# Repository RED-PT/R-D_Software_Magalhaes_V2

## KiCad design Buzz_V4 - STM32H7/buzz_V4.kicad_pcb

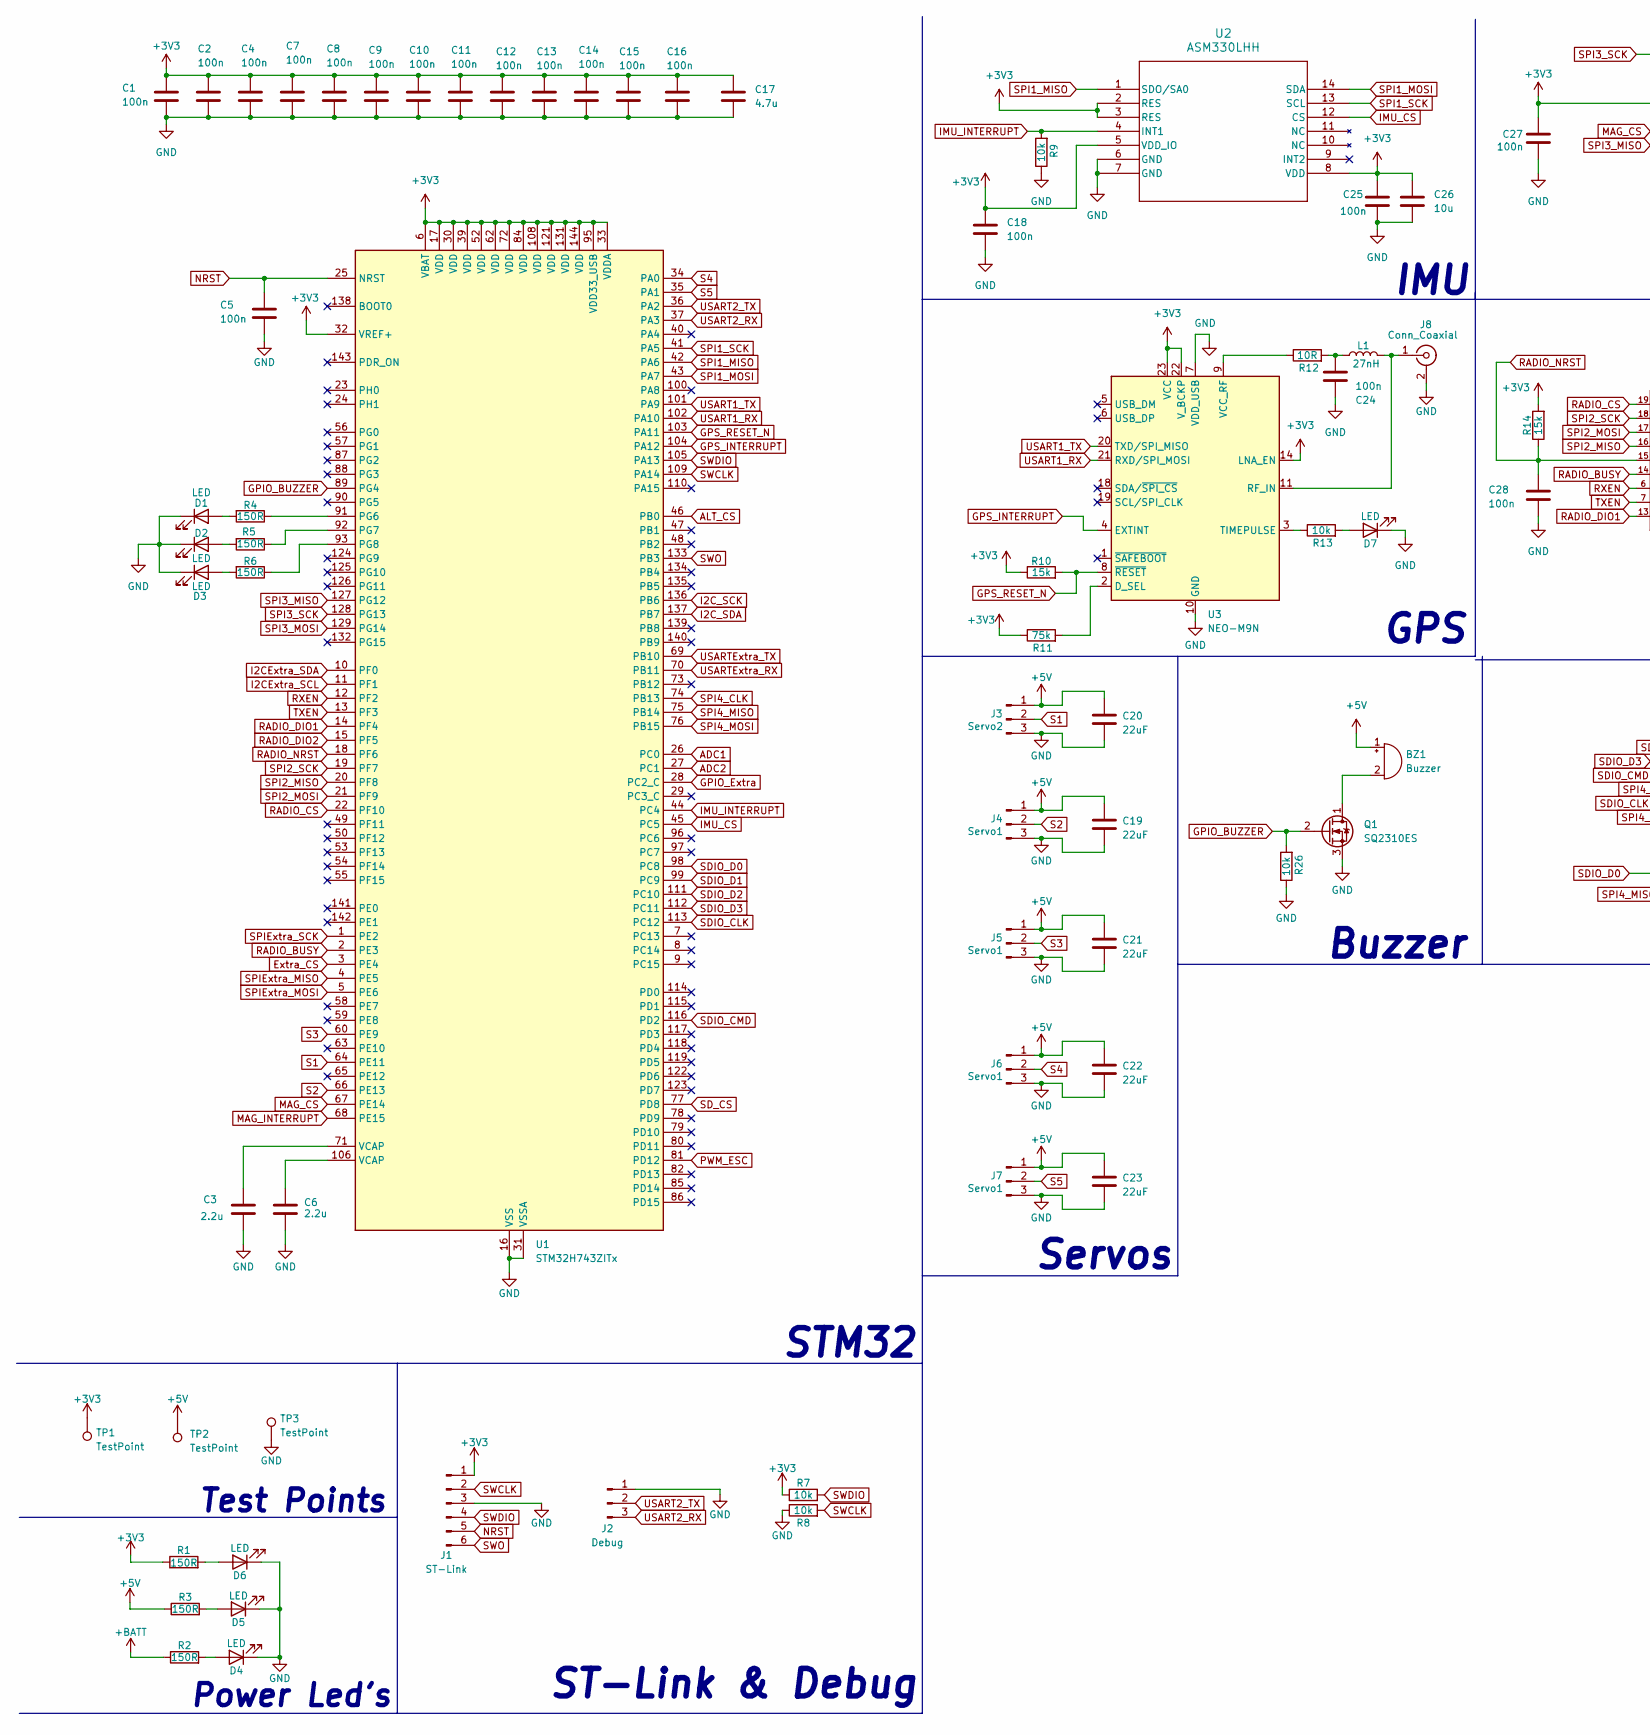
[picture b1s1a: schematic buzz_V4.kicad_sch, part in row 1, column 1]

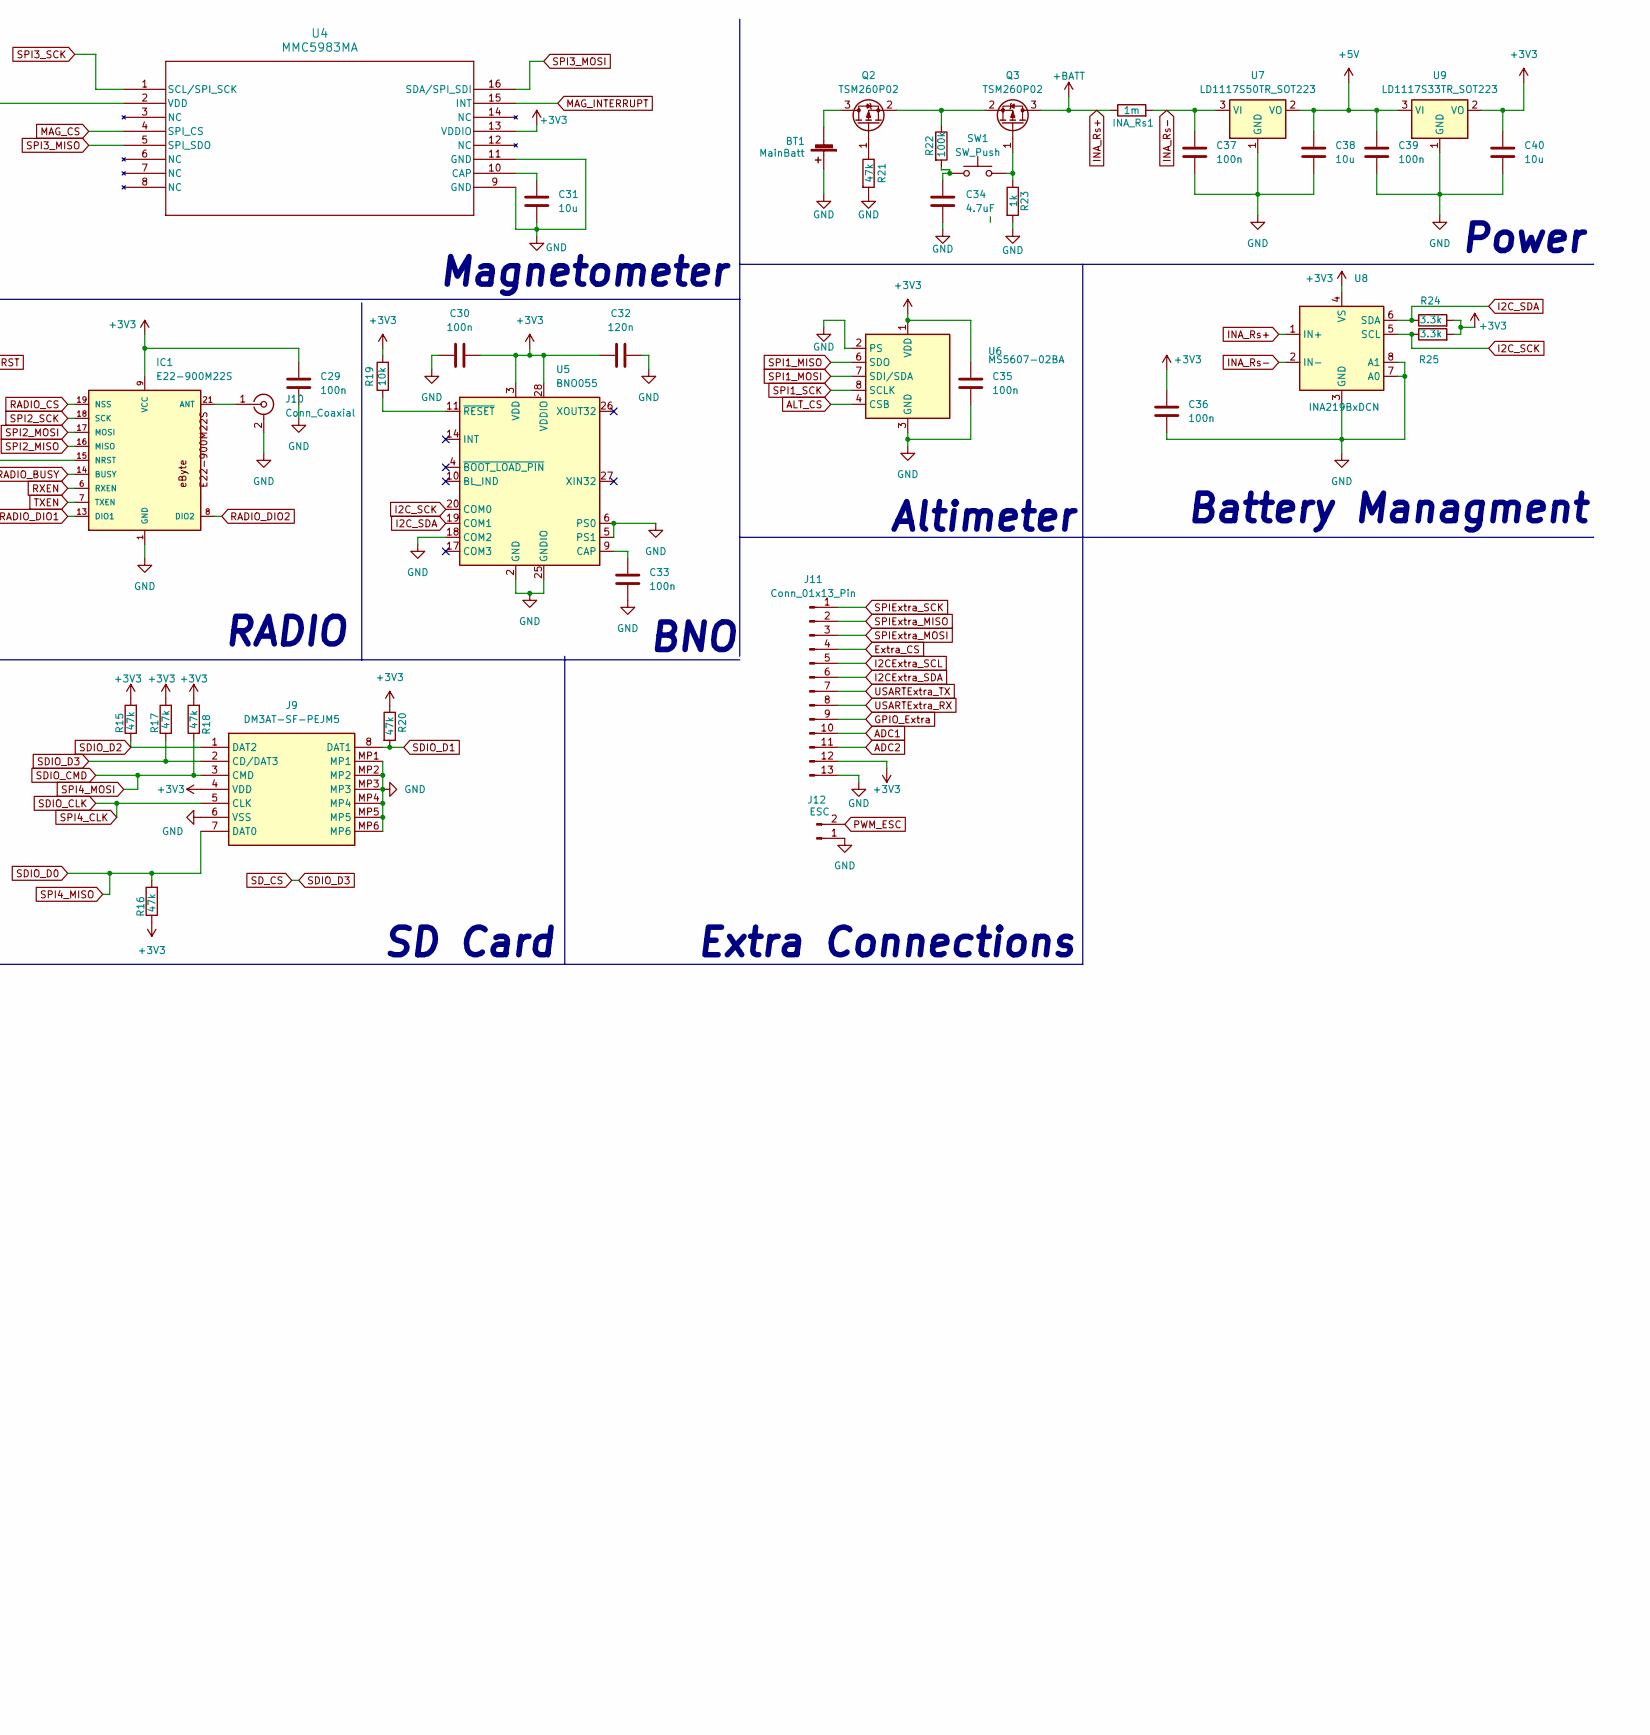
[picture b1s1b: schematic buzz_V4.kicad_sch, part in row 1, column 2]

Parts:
BT1: MainBatt; AMASS_XT30U-M_1x02_P5.0mm_Vertical
BZ1: Buzzer; Buzzer_12x9.5RM7.6
C1, C2, C4, C5, C7, C8, C9, C10, C11, C12, C13, C14, C15, C16, C18, C24, C25, C27, C28, C29, C30, C33, C35, C36, C37, C39: 100n; C_1206_3216Metric_Pad1.33x1.80mm_HandSolder
C3, C6: 2.2u; C_1206_3216Metric_Pad1.33x1.80mm_HandSolder
C17: 4.7u; C_1206_3216Metric_Pad1.33x1.80mm_HandSolder
C19, C20, C21, C22, C23: 22uF; C_1206_3216Metric_Pad1.33x1.80mm_HandSolder
C26, C31, C38, C40: 10u; C_1206_3216Metric_Pad1.33x1.80mm_HandSolder
C32: 120n; C_1206_3216Metric_Pad1.33x1.80mm_HandSolder
C34: 4.7uF; C_1206_3216Metric_Pad1.33x1.80mm_HandSolder
D1, D2, D3, D4, D5, D6, D7: LED; LED_0805_2012Metric_Pad1.15x1.40mm_HandSolder
IC1: E22-900M22S
INA_Rs1: 1m; R_2512_6332Metric_Pad1.40x3.35mm_HandSolder
J1: ST-Link; PinHeader_1x06_P2.54mm_Vertical
J2: Debug; PinHeader_1x03_P2.54mm_Vertical
J3: Servo2; PinHeader_1x03_P2.54mm_Vertical
J4, J5, J6, J7: Servo1; PinHeader_1x03_P2.54mm_Vertical
J8: Conn_Coaxial; U.FL_Molex_MCRF_73412-0110_Vertical
J9: DM3AT-SF-PEJM5; DM3ATSFPEJM5; Mouser Part Number 798-DM3AT-SF-PEJM5
J10: Conn_Coaxial; SMA_Amphenol_132134-10_Vertical
J11: Conn_01x13_Pin; PinHeader_1x13_P2.54mm_Vertical
J12: ESC; PinHeader_1x02_P2.54mm_Vertical
L1: 27nH; L_0603_1608Metric_Pad1.05x0.95mm_HandSolder
Q1: SQ2310ES; SOT-23
Q2, Q3: TSM260P02; SOT-23
R1, R2, R3, R4, R5, R6: 150R; R_0805_2012Metric_Pad1.20x1.40mm_HandSolder
R7, R8, R9, R13, R19, R26: 10k; R_0805_2012Metric_Pad1.20x1.40mm_HandSolder
R10, R14: 15k; R_0805_2012Metric_Pad1.20x1.40mm_HandSolder
R11: 75k; R_0805_2012Metric_Pad1.20x1.40mm_HandSolder
R12: 10R; R_0805_2012Metric_Pad1.20x1.40mm_HandSolder
R15, R16, R17, R18, R20, R21: 47k; R_0805_2012Metric_Pad1.20x1.40mm_HandSolder
R22: 100k; R_0805_2012Metric_Pad1.20x1.40mm_HandSolder
R23: 1k; R_0805_2012Metric_Pad1.20x1.40mm_HandSolder
R24, R25: 3.3k; R_0805_2012Metric_Pad1.20x1.40mm_HandSolder
SW1: SW_Push; SW_PUSH_6mm
TP1, TP2, TP3: TestPoint; TestPoint_Plated_Hole_D2.0mm
U1: STM32H743ZITx; LQFP-144_20x20mm_P0.5mm
U2: ASM330LHH; LGA-14L_2P5X3X0P83_STM
U3: NEO-M9N; ublox_NEO
U4: MMC5983MA; MMC5983MA_MEM
U5: BNO055; LGA-28_5.2x3.8mm_P0.5mm
U6: MS5607-02BA; LGA-8_3x5mm_P1.25mm
U7: LD1117S50TR_SOT223; SOT-223-3_TabPin2
U8: INA219BxDCN; SOT-23-8
U9: LD1117S33TR_SOT223; SOT-223-3_TabPin2

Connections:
+3V3: C1.1, C2.1, C4.1, C7.1, C8.1, C9.1, C10.1, C11.1, C12.1, C13.1, C14.1, C15.1, C16.1, C17.1, C18.1, C25.1, C26.1, C27.1, C29.1, C30.2, C32.1, C35.1, C36.1, C40.1, IC1.9 (VCC), J1.1, J9.4 (VDD), J11.12, R1.1, R7.1, R10.1, R11.1, R14.2, R15.2, R16.1, R17.2, R18.2, R19.2, R20.1, R24.2, R25.2, TP1.1, U1.6 (VBAT), U1.17 (VDD), U1.30 (VDD), U1.32 (VREF+), U1.33 (VDDA), U1.39 (VDD), U1.52 (VDD), U1.62 (VDD), U1.72 (VDD), U1.84 (VDD), U1.95 (VDD33_USB), U1.108 (VDD), U1.121 (VDD), U1.131 (VDD), U1.144 (VDD), U2.2 (RES), U2.3 (RES), U2.5 (VDD_IO), U2.8 (VDD), U3.14 (LNA_EN), U3.22 (V_BCKP), U3.23 (VCC), U4.2 (VDD), U4.13 (VDDIO), U5.3 (VDD), U5.28 (VDDIO), U6.1 (VDD), U8.4 (VS), U9.2 (VO)
+5V: BZ1.1 (+), C19.1, C20.1, C21.1, C22.1, C23.1, C38.1, C39.1, J3.1, J4.1, J5.1, J6.1, J7.1, R3.1, TP2.1, U7.2 (VO), U9.3 (VI)
ADC1: J11.10, U1.26 (PC0)
ADC2: J11.11, U1.27 (PC1)
ALT_CS: U1.46 (PB0), U6.4 (CSB), U6.5 (CSB)
Extra_CS: J11.4, U1.3 (PE4)
GND: BT1.1 (+), C1.2, C2.2, C3.2, C4.2, C5.2, C6.2, C7.2, C8.2, C9.2, C10.2, C11.2, C12.2, C13.2, C14.2, C15.2, C16.2, C17.2, C18.2, C19.2, C20.2, C21.2, C22.2, C23.2, C24.2, C25.2, C26.2, C27.2, C28.2, C29.2, C30.1, C31.2, C32.2, C33.2, C34.2, C35.2, C36.2, C37.2, C38.2, C39.2, C40.2, D1.1 (K), D2.1 (K), D3.1 (K), D4.1 (K), D5.1 (K), D6.1 (K), D7.1 (K), IC1.1 (GND), IC1.2 (GND), IC1.3 (GND), IC1.4 (GND), IC1.5 (GND), IC1.10 (GND), IC1.11 (GND), IC1.12 (GND), IC1.20 (GND), IC1.22 (GND), J1.3, J2.1, J3.3, J4.3, J5.3, J6.3, J7.3, J8.2 (Ext), J9.6 (VSS), J9.MP1, J9.MP2, J9.MP3, J9.MP4, J9.MP5, J9.MP6, J10.2 (Ext), J11.13, J12.1, Q1.3 (S), R8.1, R9.1, R21.2, R23.2, R26.1, TP3.1, U1.16 (VSS), U1.31 (VSSA), U1.38 (VSS), U1.51 (VSS), U1.61 (VSS), U1.83 (VSS), U1.94 (VSS), U1.107 (VSS), U1.120 (VSS), U1.130 (VSS), U2.6 (GND), U2.7 (GND), U3.7 (VDD_USB), U3.10 (GND), U3.12 (GND), U3.13 (GND), U3.24 (GND), U4.9 (GND), U4.11 (GND), U5.2 (GND), U5.5 (PS1), U5.6 (PS0), U5.18 (COM2), U5.25 (GNDIO), U6.2 (PS), U6.3 (GND), U7.1 (GND), U8.3 (GND), U8.7 (A0), U8.8 (A1), U9.1 (GND)
GPIO_BUZZER: Q1.2 (G), R26.2, U1.89 (PG4)
GPIO_Extra: J11.9, U1.28 (PC2_C)
GPS_INTERRUPT: U1.104 (PA12), U3.4 (EXTINT)
GPS_RESET_N: R10.2, U1.103 (PA11), U3.8 (~RESET)
I2CExtra_SCL: J11.5, U1.11 (PF1)
I2CExtra_SDA: J11.6, U1.10 (PF0)
I2C_SCK: R25.1, U1.136 (PB6), U5.20 (COM0), U8.5 (SCL)
I2C_SDA: R24.1, U1.137 (PB7), U5.19 (COM1), U8.6 (SDA)
IMU_CS: U1.45 (PC5), U2.12 (CS)
IMU_INTERRUPT: R9.2, U1.44 (PC4), U2.4 (INT1)
INA_Rs+: INA_Rs1.1, Q3.3 (D), R2.1, U8.1 (IN+)
INA_Rs-: C37.1, INA_Rs1.2, U7.3 (VI), U8.2 (IN-)
MAG_CS: U1.67 (PE14), U4.4 (SPI_CS)
MAG_INTERRUPT: U1.68 (PE15), U4.15 (INT)
NRST: C5.1, J1.5, U1.25 (NRST)
unnamed: BT1.2 (-), Q2.3 (D)
unnamed: BZ1.2 (-), Q1.1 (D)
unnamed: C3.1, U1.71 (VCAP)
unnamed: C6.1, U1.106 (VCAP)
unnamed: C24.1, L1.1, R12.2
unnamed: C34.1, R22.2, SW1.1
unnamed: D1.2 (A), R4.2
unnamed: D2.2 (A), R5.2
unnamed: D3.2 (A), R6.2
unnamed: D4.2 (A), R2.2
unnamed: D5.2 (A), R3.2
unnamed: D6.2 (A), R1.2
unnamed: D7.2 (A), R13.2
unnamed: IC1.21 (ANT), J10.1 (In)
unnamed: J8.1 (In), L1.2, U3.11 (RF_IN)
unnamed: Q2.1 (G), R21.1
unnamed: Q2.2 (S), Q3.2 (S), R22.1
unnamed: Q3.1 (G), R23.1, SW1.2
unnamed: R4.1, U1.91 (PG6)
unnamed: R5.1, U1.92 (PG7)
unnamed: R6.1, U1.93 (PG8)
unnamed: R11.2, U3.2 (D_SEL)
unnamed: R13.1, U3.3 (TIMEPULSE)
unnamed: R12.1, U3.9 (VCC_RF)
unnamed: C31.1, U4.10 (CAP)
unnamed: C33.1, U5.9 (CAP)
unnamed: R19.1, U5.11 (~RESET)
PWM_ESC: J12.2, U1.81 (PD12)
RADIO_BUSY: IC1.14 (BUSY), U1.2 (PE3)
RADIO_CS: IC1.19 (NSS), U1.22 (PF10)
RADIO_DIO1: IC1.13 (DIO1), U1.14 (PF4)
RADIO_DIO2: IC1.8 (DIO2), U1.15 (PF5)
RADIO_NRST: C28.1, IC1.15 (NRST), R14.1, U1.18 (PF6)
RXEN: IC1.6 (RXEN), U1.12 (PF2)
S1: J3.2, U1.64 (PE11)
S2: J4.2, U1.66 (PE13)
S3: J5.2, U1.60 (PE9)
S4: J6.2, U1.34 (PA0)
S5: J7.2, U1.35 (PA1)
SDIO_CLK: J9.5 (CLK), U1.74 (PB13), U1.113 (PC12)
SDIO_CMD: J9.3 (CMD), R18.1, U1.76 (PB15), U1.116 (PD2)
SDIO_D0: J9.7 (DAT0), R16.2, U1.75 (PB14), U1.98 (PC8)
SDIO_D1: J9.8 (DAT1), R20.2, U1.99 (PC9)
SDIO_D2: J9.1 (DAT2), R15.1, U1.111 (PC10)
SDIO_D3: J9.2 (CD/DAT3), R17.1, U1.77 (PD8), U1.112 (PC11)
SPI1_MISO: U1.42 (PA6), U2.1 (SDO/SA0), U6.6 (SDO)
SPI1_MOSI: U1.43 (PA7), U2.14 (SDA), U6.7 (SDI/SDA)
SPI1_SCK: U1.41 (PA5), U2.13 (SCL), U6.8 (SCLK)
SPI2_MISO: IC1.16 (MISO), U1.20 (PF8)
SPI2_MOSI: IC1.17 (MOSI), U1.21 (PF9)
SPI2_SCK: IC1.18 (SCK), U1.19 (PF7)
SPI3_MISO: U1.127 (PG12), U4.5 (SPI_SDO)
SPI3_MOSI: U1.129 (PG14), U4.16 (SDA/SPI_SDI)
SPI3_SCK: U1.128 (PG13), U4.1 (SCL/SPI_SCK)
SPIExtra_MISO: J11.2, U1.4 (PE5)
SPIExtra_MOSI: J11.3, U1.5 (PE6)
SPIExtra_SCK: J11.1, U1.1 (PE2)
SWCLK: J1.2, R8.2, U1.109 (PA14)
SWDIO: J1.4, R7.2, U1.105 (PA13)
SWO: J1.6, U1.133 (PB3)
TXEN: IC1.7 (TXEN), U1.13 (PF3)
USART1_RX: U1.102 (PA10), U3.21 (RXD/SPI_MOSI)
USART1_TX: U1.101 (PA9), U3.20 (TXD/SPI_MISO)
USART2_RX: J2.3, U1.37 (PA3)
USART2_TX: J2.2, U1.36 (PA2)
USARTExtra_RX: J11.8, U1.70 (PB11)
USARTExtra_TX: J11.7, U1.69 (PB10)

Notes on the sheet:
Battery Managment
Power Led's
Test Points
Buzzer
STM32
Servos
Magnetometer
SD Card
RADIO
Extra Connections
GPS
IMU
ST-Link & Debug
BNO
Altimeter
Power

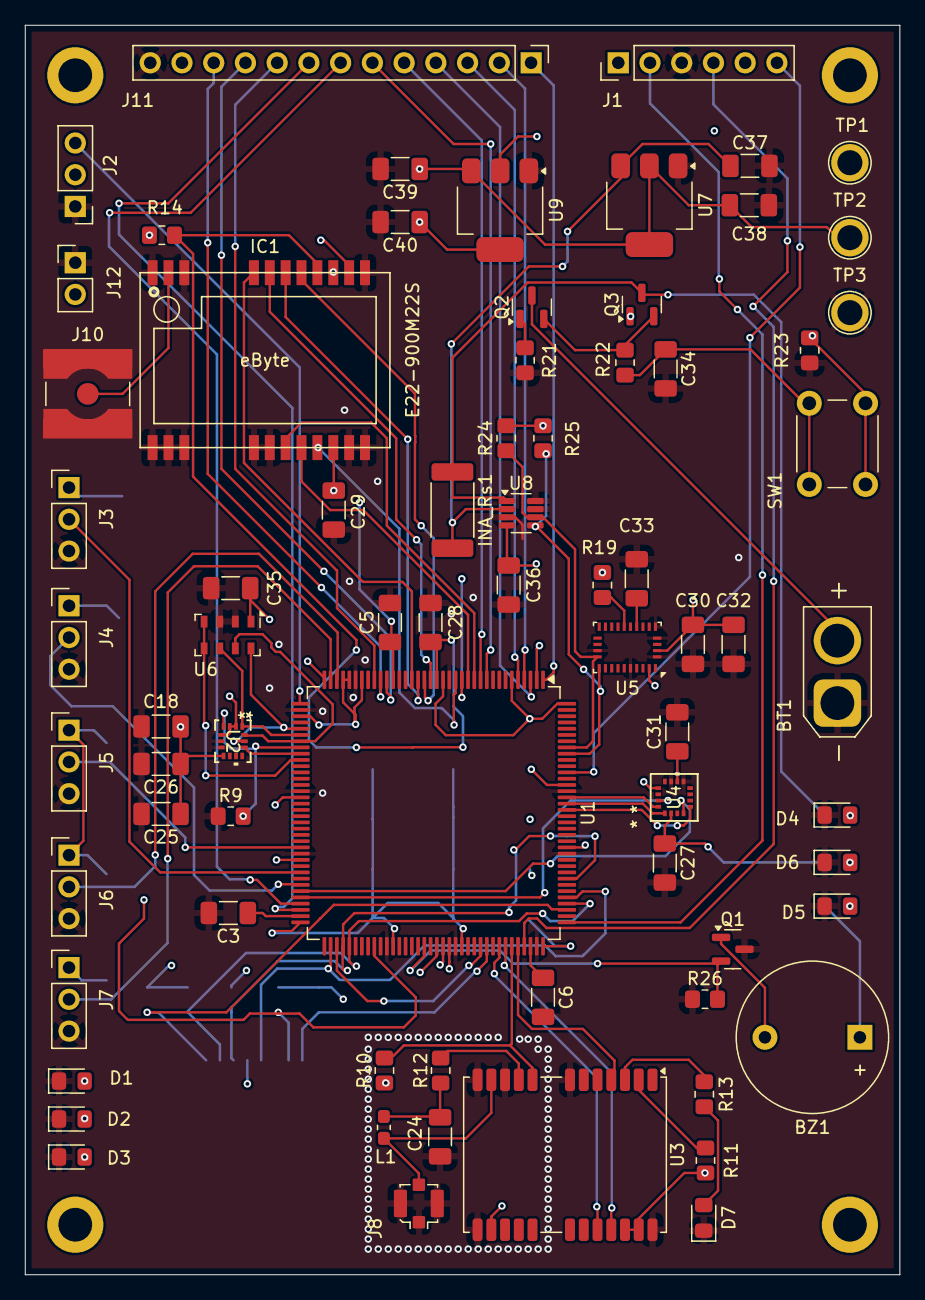
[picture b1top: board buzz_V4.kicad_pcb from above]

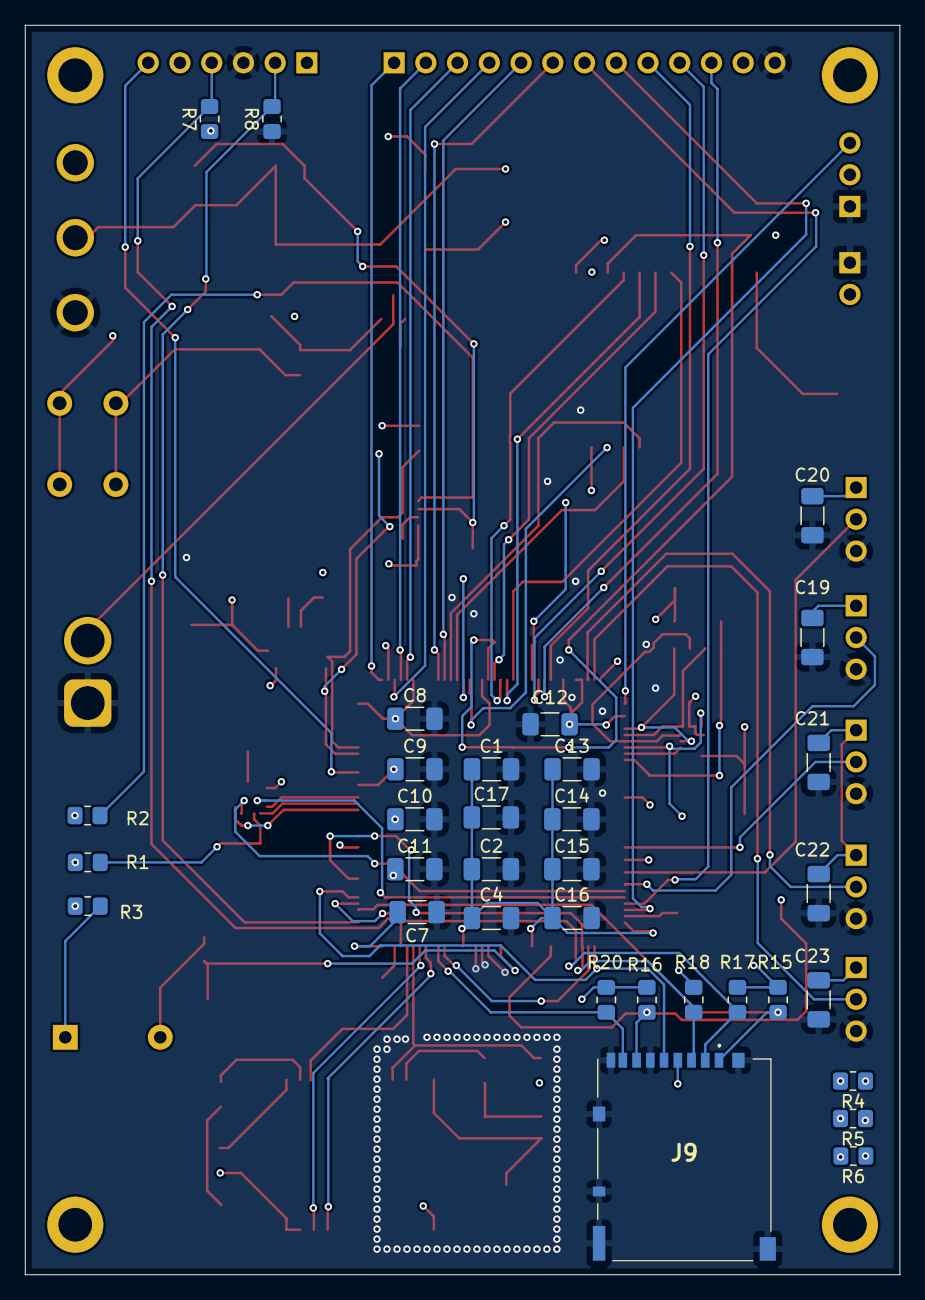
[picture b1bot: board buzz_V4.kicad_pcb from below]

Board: 4 copper layers, 70.0 x 100.0 mm, 106 parts (33 on the bottom side), 89 nets.

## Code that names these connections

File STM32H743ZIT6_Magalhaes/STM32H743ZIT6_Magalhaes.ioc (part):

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Mcu.Name=STM32H743ZITx
Mcu.Package=LQFP144
Mcu.UserName=STM32H743ZITx
PA0.Signal=S_TIM2_CH1_ETR
PA1.Signal=S_TIM2_CH2
PA10.Mode=Asynchronous
PA10.Signal=USART1_RX
PA11.GPIOParameters=PinState,GPIO_Label
PA11.GPIO_Label=GPS_RESET_N
PA11.PinState=GPIO_PIN_SET
PA11.Signal=GPIO_Output
PA12.GPIOParameters=GPIO_Label,GPIO_ModeDefaultEXTI
PA12.GPIO_Label=GPS_INTERRUPT
PA12.GPIO_ModeDefaultEXTI=GPIO_MODE_IT_RISING
PA12.Signal=GPXTI12
PA13\ (JTMS/SWDIO).Mode=Serial_Wire
PA13\ (JTMS/SWDIO).Signal=DEBUG_JTMS-SWDIO
PA14\ (JTCK/SWCLK).Mode=Serial_Wire
PA14\ (JTCK/SWCLK).Signal=DEBUG_JTCK-SWCLK
PA2.Mode=Asynchronous
PA2.Signal=USART2_TX
PA3.Mode=Asynchronous
PA3.Signal=USART2_RX
PA5.Mode=Full_Duplex_Master
PA5.Signal=SPI1_SCK
PA6.Mode=Full_Duplex_Master
PA6.Signal=SPI1_MISO
PA7.Mode=Full_Duplex_Master
PA7.Signal=SPI1_MOSI
PA9.Mode=Asynchronous
PA9.Signal=USART1_TX
PB0.GPIOParameters=PinState,GPIO_Label
PB0.GPIO_Label=ALT_CS
PB0.PinState=GPIO_PIN_SET
PB0.Signal=GPIO_Output
PB13.GPIOParameters=GPIO_PuPd
PB13.GPIO_PuPd=GPIO_PULLUP
PB13.Mode=Full_Duplex_Master
PB13.Signal=SPI2_SCK
PB14.GPIOParameters=GPIO_PuPd
PB14.GPIO_PuPd=GPIO_PULLUP
PB14.Mode=Full_Duplex_Master
PB14.Signal=SPI2_MISO
PB15.GPIOParameters=GPIO_PuPd
PB15.GPIO_PuPd=GPIO_PULLUP
PB15.Mode=Full_Duplex_Master
PB15.Signal=SPI2_MOSI
PB6.Mode=I2C
PB6.Signal=I2C1_SCL
PB7.Mode=I2C
PB7.Signal=I2C1_SDA
PC5.GPIOParameters=PinState,GPIO_Label
PC5.GPIO_Label=IMU_CS
PC5.PinState=GPIO_PIN_SET
PC5.Signal=GPIO_Output
PD12.GPIOParameters=GPIO_Label
PD12.GPIO_Label=PWM_ESC
PD12.Signal=S_TIM4_CH1
PD8.GPIOParameters=PinState,GPIO_Label
PD8.GPIO_Label=SD_CS
PD8.PinState=GPIO_PIN_SET
PD8.Signal=GPIO_Output
PE11.Signal=S_TIM1_CH2
PE13.Signal=S_TIM1_CH3
PE14.GPIOParameters=PinState,GPIO_Label
PE14.GPIO_Label=MAG_CS
PE14.PinState=GPIO_PIN_SET
PE14.Signal=GPIO_Output
PE15.GPIOParameters=GPIO_Label
PE15.GPIO_Label=MAG_INTERRUPT
PE15.Signal=GPXTI15
PE3.GPIOParameters=GPIO_PuPd,GPIO_Label
PE3.GPIO_Label=RADIO_BUSY
PE3.GPIO_PuPd=GPIO_PULLDOWN
PE3.Signal=GPIO_Input
PF10.GPIOParameters=PinState,GPIO_Label
PF10.GPIO_Label=RADIO_CS
PF10.PinState=GPIO_PIN_SET
PF10.Signal=GPIO_Output
PF2.GPIOParameters=GPIO_Label
PF2.GPIO_Label=RXEN
PF2.Signal=GPIO_Output
PF3.GPIOParameters=GPIO_Label
PF3.GPIO_Label=TXEN
PF3.Signal=GPIO_Output
PF4.GPIOParameters=GPIO_Label,GPIO_ModeDefaultEXTI
PF4.GPIO_Label=RADIO_DIO1
PF4.GPIO_ModeDefaultEXTI=GPIO_MODE_IT_RISING
PF4.Signal=GPXTI4
PF5.GPIOParameters=GPIO_Label
PF5.GPIO_Label=RADIO_DIO2
PF5.Signal=GPXTI5
PF6.GPIOParameters=PinState,GPIO_Label
PF6.GPIO_Label=RADIO_NRST
PF6.PinState=GPIO_PIN_SET
PF6.Signal=GPIO_Output
PF7.Mode=Full_Duplex_Master
PF7.Signal=SPI5_SCK
PF8.Mode=Full_Duplex_Master
PF8.Signal=SPI5_MISO
PF9.Mode=Full_Duplex_Master
PF9.Signal=SPI5_MOSI
PG12.Mode=Full_Duplex_Master
PG12.Signal=SPI6_MISO
PG13.Mode=Full_Duplex_Master
PG13.Signal=SPI6_SCK
PG14.Mode=Full_Duplex_Master
PG14.Signal=SPI6_MOSI
PG4.GPIOParameters=GPIO_Label
PG4.GPIO_Label=GPIO_BUZZER
PG4.Signal=GPIO_Output
PG6.Signal=GPIO_Output
PG7.Signal=GPIO_Output
PG8.Signal=GPIO_Output
RCC.SYSCLKFreq_VALUE=480000000
RCC.SYSCLKSource=RCC_SYSCLKSOURCE_PLLCLK
board=custom

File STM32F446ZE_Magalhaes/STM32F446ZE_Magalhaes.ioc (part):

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Mcu.Name=STM32F446Z(C-E)Tx
Mcu.Package=LQFP144
Mcu.UserName=STM32F446ZETx
PA10.Mode=Asynchronous
PA10.Signal=USART1_RX
PA13.GPIOParameters=GPIO_Label
PA13.GPIO_Label=TMS
PA13.Mode=Serial_Wire
PA13.Signal=SYS_JTMS-SWDIO
PA14.GPIOParameters=GPIO_Label
PA14.GPIO_Label=TCK
PA14.Mode=Serial_Wire
PA14.Signal=SYS_JTCK-SWCLK
PA3.Mode=Asynchronous
PA3.Signal=USART2_RX
PA9.Mode=Asynchronous
PA9.Signal=USART1_TX
PB0.GPIOParameters=GPIO_Label
PB0.GPIO_Label=LD1 [Green]
PB0.Signal=GPIO_Output
PB1.GPIOParameters=GPIO_Speed,PinState,GPIO_Label,GPIO_ModeDefaultOutputPP
PB1.GPIO_Label=IMU_CS
PB1.GPIO_ModeDefaultOutputPP=GPIO_MODE_OUTPUT_PP
PB1.GPIO_Speed=GPIO_SPEED_FREQ_VERY_HIGH
PB1.PinState=GPIO_PIN_RESET
PB1.Signal=GPIO_Output
PB10.Mode=Full_Duplex_Master
PB10.Signal=SPI2_SCK
PB13.GPIOParameters=GPIO_Speed,PinState,GPIO_Label
PB13.GPIO_Label=MAG_CS
PB13.GPIO_Speed=GPIO_SPEED_FREQ_VERY_HIGH
PB13.PinState=GPIO_PIN_SET
PB13.Signal=GPIO_Output
PB14.GPIOParameters=GPIO_Label
PB14.GPIO_Label=LD3 [Red]
PB14.Signal=GPIO_Output
PB2.GPIOParameters=GPIO_PuPd,GPIO_Label
PB2.GPIO_Label=LORA_DIO0
PB2.GPIO_PuPd=GPIO_NOPULL
PB2.Signal=GPXTI2
PB3.GPIOParameters=GPIO_PuPd
PB3.GPIO_PuPd=GPIO_NOPULL
PB3.Mode=Full_Duplex_Master
PB3.Signal=SPI1_SCK
PB4.GPIOParameters=GPIO_PuPd
PB4.GPIO_PuPd=GPIO_NOPULL
PB4.Mode=Full_Duplex_Master
PB4.Signal=SPI1_MISO
PB5.GPIOParameters=GPIO_PuPd
PB5.GPIO_PuPd=GPIO_NOPULL
PB5.Mode=Full_Duplex_Master
PB5.Signal=SPI1_MOSI
PB6.GPIOParameters=GPIO_Pu
PB6.GPIO_Pu=GPIO_PULLUP
PB6.Mode=I2C
PB6.Signal=I2C1_SCL
PB7.GPIOParameters=GPIO_Label
PB7.GPIO_Label=LD2 [Blue]
PB7.Signal=GPIO_Output
PB9.GPIOParameters=GPIO_Pu
PB9.GPIO_Pu=GPIO_NOPULL
PB9.Mode=I2C
PB9.Signal=I2C1_SDA
PC10.Mode=Full_Duplex_Master
PC10.Signal=SPI3_SCK
PC11.Mode=Full_Duplex_Master
PC11.Signal=SPI3_MISO
PC13.GPIOParameters=GPIO_Label
PC13.GPIO_Label=USER_Btn [B1]
PC13.Signal=GPXTI13
PC2.Mode=Full_Duplex_Master
PC2.Signal=SPI2_MISO
PC3.Mode=Full_Duplex_Master
PC3.Signal=SPI2_MOSI
PC6.Signal=S_TIM3_CH1
PD0.Mode=Full_Duplex_Master
PD0.Signal=SPI3_MOSI
PD14.GPIOParameters=GPIO_Label
PD14.GPIO_Label=CS_SD
PD14.Signal=GPIO_Output
PD15.GPIOParameters=GPIO_Label
PD15.GPIO_Label=CS_BARO
PD15.Signal=GPIO_Output
PD5.Mode=Asynchronous
PD5.Signal=USART2_TX
PD8.GPIOParameters=GPIO_Label
PD8.GPIO_Label=STLK_RX [STM32F103CBT6_PA3]
PD8.Mode=Asynchronous
PD8.Signal=USART3_TX
PD9.GPIOParameters=GPIO_Label
PD9.GPIO_Label=STLK_TX [STM32F103CBT6_PA2]
PD9.Mode=Asynchronous
PD9.Signal=USART3_RX
PE2.GPIOParameters=GPIO_PuPd
PE2.GPIO_PuPd=GPIO_PULLUP
PE2.Mode=Full_Duplex_Master
PE2.Signal=SPI4_SCK
PE5.GPIOParameters=GPIO_PuPd
PE5.GPIO_PuPd=GPIO_PULLUP
PE5.Mode=Full_Duplex_Master
PE5.Signal=SPI4_MISO
PE6.GPIOParameters=GPIO_PuPd
PE6.GPIO_PuPd=GPIO_PULLUP
PE6.Mode=Full_Duplex_Master
PE6.Signal=SPI4_MOSI
PE9.Signal=S_TIM1_CH1
PF0.GPIOParameters=GPIO_Pu
PF0.GPIO_Pu=GPIO_PULLUP
PF0.Mode=I2C
PF0.Signal=I2C2_SDA
PF1.GPIOParameters=GPIO_Pu
PF1.GPIO_Pu=GPIO_PULLUP
PF1.Mode=I2C
PF1.Signal=I2C2_SCL
PF9.GPIOParameters=GPIO_Speed,PinState,GPIO_Label
PF9.GPIO_Label=LORA_M0
PF9.GPIO_Speed=GPIO_SPEED_FREQ_VERY_HIGH
PF9.PinState=GPIO_PIN_SET
PF9.Signal=GPIO_Output
PG0.GPIOParameters=GPIO_Speed,PinState,GPIO_Label
PG0.GPIO_Label=LORA_M1
PG0.GPIO_Speed=GPIO_SPEED_FREQ_VERY_HIGH
PG0.PinState=GPIO_PIN_SET
PG0.Signal=GPIO_Output
PG1.GPIOParameters=GPIO_Speed,PinState,GPIO_Label
PG1.GPIO_Label=LORA_CS
PG1.GPIO_Speed=GPIO_SPEED_FREQ_VERY_HIGH
PG1.PinState=GPIO_PIN_SET
PG1.Signal=GPIO_Output
PG14.Mode=Asynchronous
PG14.Signal=USART6_TX
PG9.Mode=Asynchronous
PG9.Signal=USART6_RX
PH0-OSC_IN.GPIOParameters=GPIO_Label
PH0-OSC_IN.GPIO_Label=MCO [STM32F103CBT6_PA8]
PH0-OSC_IN.Mode=HSE-External-Clock-Source
PH0-OSC_IN.Signal=RCC_OSC_IN
PH1-OSC_OUT.Mode=HSE-External-Clock-Source
PH1-OSC_OUT.Signal=RCC_OSC_OUT
RCC.HSE_VALUE=8000000
RCC.SYSCLKFreq_VALUE=168000000
RCC.SYSCLKSource=RCC_SYSCLKSOURCE_PLLCLK
RCC.SYSCLKSourceVirtual=RCC_SYSCLKSOURCE_PLLCLK
board=NUCLEO-F446ZE
boardIOC=true

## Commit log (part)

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2025-10-03 Inicial Setup
    Main Project:
    - R-D_Software_Magalhaes_V2
    STM Projects:
    - STM32F413ZH_Magalhaes
    - STM32F446ZE_Magalhaes
2025-10-03 Add FreeRTOS and FatFs integration for STM32 projects
    Integrated FreeRTOS and FatFs middleware, configuration, and drivers for STM32F413ZH and STM32F446ZE projects. Updated .cproject and .mxproject to include new source and include paths. Added user dis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
2025-10-03 Setup
    Refactored user_diskio.c to remove SD card-specific code and stub out disk functions.
2025-10-06 Add thread creation and update STM32 drivers
    Introduced create_threads module with header for FreeRTOS thread management. Added config.h to both STM32F413ZH and STM32F446ZE projects. Updated STM32F446ZE project files to add I2C, SD, MMC, SPI, a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
2025-10-07 Add flight computer module and sensor structs
    Introduced flight_computer.c and flight_computer.h with FSM state, substate, and profile enums. Expanded defs.h to include detailed sensor data structures for IMU, magnetometer, orientation IMU, baro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
2025-10-07 Add FSM context and telemetry modules
    Introduced FSM context and related functions in flight_computer.c/h, expanded FSM state, substate, profile, and event definitions. Added initial telemetry.c/h files with telemetry packet structures. 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
2025-10-07 MS5607 Drivers
2025-10-07 Add GPS sensor module and update project configs
    Introduced GPS sensor support with new gps.c and gps.h files, including parsing and validation of NMEA messages. Updated defs.h to use dec_latitude and dec_longitude for GPS coordinates. Added test.h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
2025-10-08 Add ASM330LHHX sensor and thread management modules
    Added ASM330LHHX sensor driver files (asm330lhhx_reg.c/h) and new thread management modules (threads.c/h). Updated MS5607SPI.h and thread creation files to integrate new sensor and threading function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
2025-10-09 Add FSM thread and update telemetry/flight profiles
    Introduced FSM thread creation in create_threads.c and its declaration in create_threads.h. Added new flight profile NO_PROFILE in flight_computer.h. Updated telemetry_slow_t to include crc16 and cha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
2025-10-10 Refactor thread and flag handling, remove test code
    Removed unused test and flag files, cleaned up thread functions, and updated includes to streamline initialization and thread creation. The changes improve code organization and remove obsolete buffe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
2025-10-12 Add thread structure and flash data handler system
    Introduces dedicated thread source/header files for sensors, data handler, estimator, controller, SD card, telemetry, FSM, and GPS. Implements a flash-based circular buffer system for sensor data man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
2025-10-13 Refactor data handler and sensor threads for RAM buffers
    Replaced flash-based circular buffers with RAM-based buffers in the data handler and updated all related functions and structures. Refactored sensor thread to use DMA buffers and notification-based e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
2025-10-14 Add ASM330LHHX IMU driver and integrate with sensor thread
    Added ASM330LHHX.c and ASM330LHHX.h for IMU driver implementation. Integrated the new driver into sensors_thread.c, replacing previous stub functions and updating processing logic. Updated sensors_th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
2025-10-16 Add sensor drivers and refactor sensor thread
    Added new driver implementations and headers for BNO055, MMC5983MA, and MS5607 sensors. Refactored ASM330LHHX driver for improved DMA handling and modularity. Updated sensors_thread.c to use new sens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
2025-10-17 Rename CONFIG state to CONFIGED and update comment
    Changed the enum value CONFIG to CONFIGED in flight_computer.h for clarity. Updated a comment in sensors_thread.c to clarify timer callback behavior.
2025-10-17 Initialize profile type and condense timer creation
    Set fsm_ctx.profile.type to NO_PROFILE during FSM initialization for proper default state. Refactored timer creation in create_threads.c to single-line statements for improved readability.
2025-10-17 Change printf format specifier from %lu to %u
    Updated memory usage print statements to use %u instead of %lu for buffer size output, ensuring correct format for unsigned int values.
2025-10-19 Implement BNO055 sensor driver with DMA and parsing
    Added full register definitions, operation and power modes, and calibration status macros to BNO055.h. Implemented initialization, configuration, DMA read, buffer parsing, and data conversion functio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
2025-10-19 Refactor thread initialization and improve logging
    Added missing header includes to thread source files and standardized thread startup messages with printf. Updated thread stack sizes and priorities for better resource management. Improved error and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
2025-10-19 Integrate GPS with DMA and update sensor thread
    Replaces legacy GPS thread with a new UBLOX GPS driver using DMA for UART reception. Updates sensor thread to handle GPS data and notifications, adds GPS statistics, and refactors thread creation and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
2025-11-02 Send sensor packets only to estimator queue
    Modified data_handler_store_* functions to send sensor data packets directly to the estimator queue instead of distributing to all queues immediately. Added comments explaining that the data handler 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
2025-11-05 Add LoRa SX1276 driver and improve data handler
    Introduces new LoRa SX1276 driver files (lora_sx1276.c/h) with DMA support and configuration API. Refactors data_handler_thread.c for periodic buffer flushing, overflow management, and improved telem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
2025-11-12 Add sensor simulation framework and update hardware configs
    Introduced test.c and test.h for a configurable sensor simulation framework supporting IMU, magnetometer, barometer, BNO055, and GPS data generation. Updated .cproject to adjust source paths and enab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
2025-11-15 Refactor MS5607 driver and update sensor handling
    Replaces the MS5607 altimeter driver with a simplified, corrected version that fixes bit shift errors in pressure calculation, removes the old MS5607SPI files, and updates the API to a blocking read 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
2025-11-18 Refactor data handling and add radio thread
    Major refactor of the data handler to use threshold-based flushing, improved buffer management, and FreeRTOS notifications. Added radio_thread for LoRa command/telemetry handling, with supporting hea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
2025-11-20 Integrate SX126x LoRa driver and refactor radio/telemetry
    Added new SX126x LoRa driver (lora_sx126x.c/h) and CRC16 module for radio communication. Refactored radio_thread to use the new driver, handle command packets with CRC, and improved ground station pi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
2025-11-27 Add E22 UART DMA radio driver and integrate with telemetry
    Introduces new E22 UART DMA driver files and integrates E22 radio into the telemetry and radio threads, replacing SX126x. Updates config, main, and interrupt files to support USART6 and DMA for E22. 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
2025-11-27 Improve radio packet handling and sync logic
    Refactored radio_thread_function to accumulate incoming bytes in a buffer, process complete command packets, and handle synchronization loss by shifting the buffer. Updated command_packet_t in teleme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
2025-11-29 Refactor telemetry and radio packet handling
    Major refactor of telemetry packet structures and build functions for clarity and scaling, including new packed types and updated CRC handling. Radio thread now uses a robust RX packet accumulator fo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
2025-12-02 Implement FSM boot and state management logic
    Major refactor and implementation of the flight computer FSM, including boot status tracking, state transitions, command and event handling, and thread-safe context access. Added detailed boot report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
2025-12-02 Remove unused code and minor improvements
    Deleted the unused Read_All_Files function from fatfs_funcoes_auxiliares.c and removed the unused event_seq variable from flight_computer_thread.c. Minor code cleanups were made in sensors_thread.c a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
2025-12-03 Integrate ESC PWM control and expand FSM for motor arm
    Added PWM_FUNCTIONS module for ESC motor control with ramping and emergency stop features. Updated controller_thread to use new PWM API, implement PID-based altitude/velocity control, and support ram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
2025-12-16 Revamp dashboard UI and features for v3 release
    Major update to the ground station dashboard: adds a help dialog, fullscreen graph and 3D view modes, auto-range reset for plots, improved RTT measurement, enhanced styling with rounded corners, yaw 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
2025-12-20 Improve GPS handling and add serial debug tool
    Added UBLOX_GPS_HAS_FLASH macro to GPS.h for module type distinction. Enhanced GPS initialization and statistics reporting in sensors_thread.c, including conditional config saving and more detailed r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
2026-01-15 Add ESC calibration and static thrust test features
    Implemented ESC min/max throttle calibration state machine and static thrust test routines in the flight computer. Added FX29 load cell driver for thrust measurement. Reduced RAM buffer and queue siz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
2026-02-11 Documentation + Bugs Solved
2026-03-24 Lets Buzz
    - New Buzz (PCB) directory
    - New STM project added STM32H743ZIT6
    - Configuring new .ioc
2026-03-25 Port firmware to STM32H743ZIT6 (Buzz V4 PCB)
    - Replace hardcoded stm32f4xx_hal.h with config.h across 16 files
    - Add RADIO_INTERFACE_UART/SPI macros for dual radio support
    - Wrap e22_uart_dma.c/radio_thread.c UART code with #ifdef guards
    - Fix lora_sx126x.c DIO2 RF switch for E22-900M22S (external RXEN/TXEN)
    - Add DMA/BDMA buffer placement macros for Cortex-M7 D-Cache coherency
    - Add .dma_buffer/.bdma_buffer linker sections in H743 flash script
2026-03-25 Add .claude to .gitignore... Sou burro que doi...
2026-04-25 Restructure documentation around guided learning path
    - Rewrite mainpage to point into a four-page tour
    - Add docs_pages/ with getting_started, architecture_tour,
    flight_lifecycle, porting_guide
    - Define top-level @defgroup hierarchy in groups.dox so the
    Modules sidebar mirrors the system, not the file tree
    - Fix stale Doxyfile inputs (arduino_gs_software, F413 config)
2026-05-25 cenas
